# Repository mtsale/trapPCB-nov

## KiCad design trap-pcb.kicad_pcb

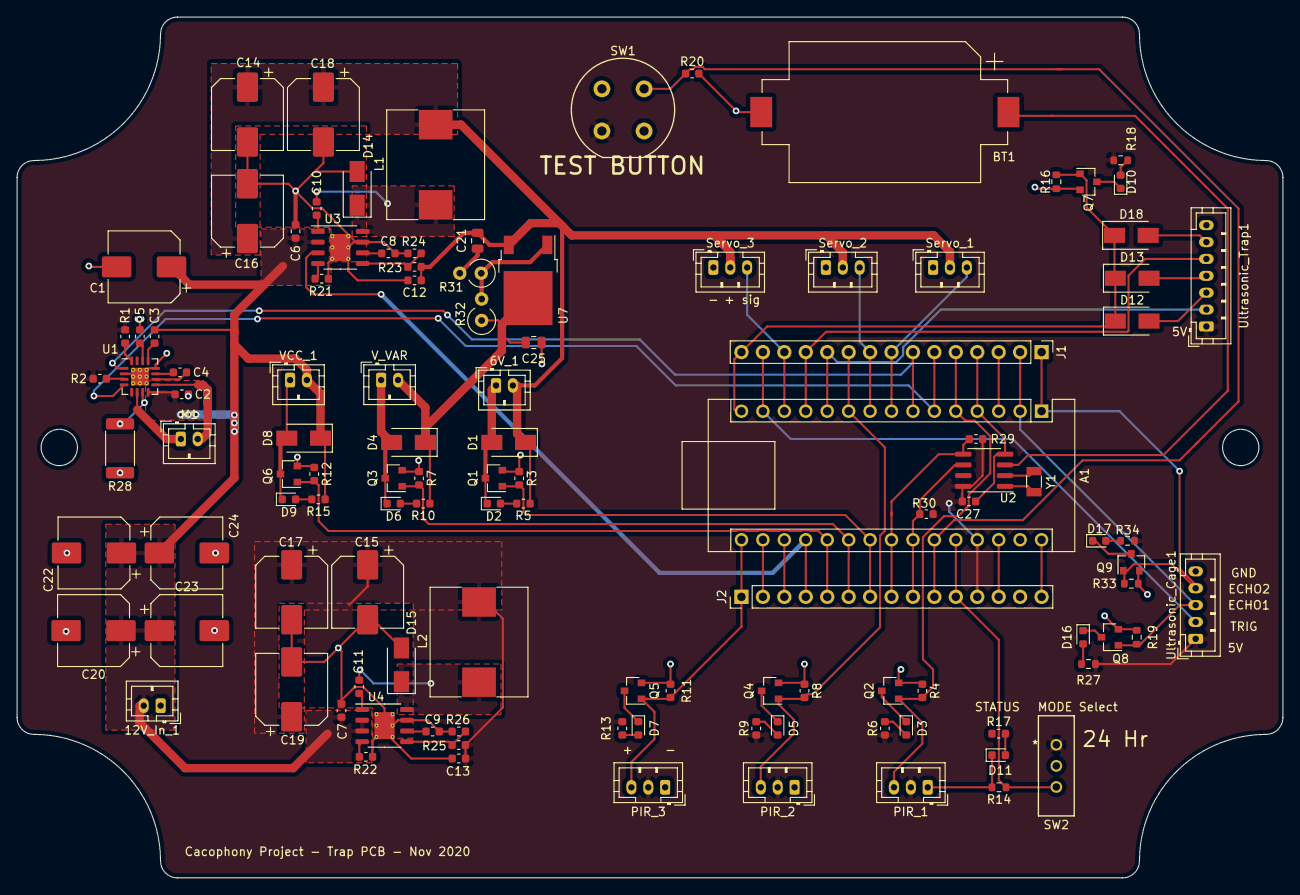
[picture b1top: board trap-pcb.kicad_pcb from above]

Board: 2 copper layers, 150.0 x 102.0 mm, 116 parts (0 on the bottom side), 77 nets.

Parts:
6V_1: CONN HEADER VERT 2POS 2MM; JST_PH_B2B-PH-K_1x02_P2.00mm_Vertical
12V_In_1: Conn_01x02; JST_PH_B2B-PH-K_1x02_P2.00mm_Vertical
A1: Arduino_Nano_v3.x; Arduino_Nano
BT1: Battery_Cell; BatteryHolder_Keystone_1060_1x2032
C1, C14, C15, C16, C17, C18, C19, C20, C22, C23, C24: 220uF; CP_Elec_8x10
C2, C3, C4, C27: 0.1uF; C_0603_1608Metric
C5: 0.22uF; C_0603_1608Metric
C6, C7: 4.7uF; C_0603_1608Metric
C8, C9: 47nF; C_0603_1608Metric
C10, C11: 100nF; C_0603_1608Metric
C12, C13: 1uF; C_0603_1608Metric
C21, C25: 22uF; C_0805_2012Metric
D1, D4, D8, D12, D13, D18: D; D_SMA
D2, D3, D5, D6, D7, D9, D10, D11, D16, D17: LED; LED_0603_1608Metric
D14, D15: D_Shockley; D_SMA
H1, H2: MountingHole; MountingHole_4.3mm_M4
J1, J2: Conn_01x15; PinHeader_1x15_P2.54mm_Vertical
L1, L2: 15uH; MWSA1004
M1: Motor_DC; JST_PH_B2B-PH-K_1x02_P2.00mm_Vertical
PIR_1, PIR_2, PIR_3: Conn_01x03; JST_PH_B3B-PH-K_1x03_P2.00mm_Vertical
Q1, Q2, Q3, Q4, Q5, Q6, Q7, Q8, Q9: Q_NMOS_GSD; SOT-23
R1, R2, R3, R4, R7, R8, R11, R12, R16, R19, R33: 100K; R_0603_1608Metric
R5, R6, R9, R10, R13, R14, R17, R18, R20, R27, R34: 470R; R_0603_1608Metric
R15: 1K; R_0603_1608Metric
R21, R22: 49K9; R_0603_1608Metric
R23: 69.8K; R_0603_1608Metric
R24, R26, R29, R30: 10K; R_0603_1608Metric
R25: 56K; R_0603_1608Metric
R28: 0.2R; R_2512_6332Metric
R31, R32: R; R_Axial_DIN0309_L9.0mm_D3.2mm_P2.54mm_Vertical
SW1: SW_DIP_x02; Push_E-Switch_KS01Q01
SW2: EG1218
Servo_1, Servo_2, Servo_3: Conn_01x03; JST_PH_B3B-PH-K_1x03_P2.00mm_Vertical
U1: DRV8800RTY; Texas_S-PWQFN-N16_EP2.1x2.1mm_ThermalVias
U2: DS1307ZN+; SOIC-8_3.9x4.9mm_P1.27mm
U3, U4: LMR16030; HTSOP-8-1EP_3.9x4.9mm_P1.27mm_EP2.4x3.2mm_ThermalVias
U7: LM317_TO-252; TO-252-2
Ultrasonic_Cage1: Conn_01x05; JST_PH_B5B-PH-K_1x05_P2.00mm_Vertical
Ultrasonic_Trap1: Conn_01x07; JST_PH_B7B-PH-K_1x07_P2.00mm_Vertical
VCC_1: CONN HEADER VERT 2POS 2MM; JST_PH_B2B-PH-K_1x02_P2.00mm_Vertical
V_VAR: CONN HEADER VERT 2POS 2MM; JST_PH_B2B-PH-K_1x02_P2.00mm_Vertical
Y1: 32.769KHz; Crystal_SMD_3215-2Pin_3.2x1.5mm

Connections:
+5V: A1.27, C13.1, C15.1, C17.1, C19.1, C27.1, J2.12, L2.2, PIR_1.2, PIR_2.2, PIR_3.2, R1.2, R2.2, R6.1, R9.1, R13.1, R18.1, R25.1, R27.1, R29.1, R30.1, R34.1, SW1.3, SW2.1, U2.8, Ultrasonic_Cage1.1, Ultrasonic_Trap1.1
+6V: 6V_1.2, C12.1, C14.1, C16.1, C18.1, C21.1, D1.1, L1.2, R5.1, R23.1, Servo_1.2, Servo_2.2, Servo_3.2, U7.3
/3.3V_1: A1.21, J2.6, Q3.1, R7.1
/6V_1: A1.22, J2.7, Q1.1, R3.1
/6V_ENABLE: A1.19, J2.4, U3.3
/ECHO_CAGE: A1.2, J1.2, Q8.1, R19.1, Ultrasonic_Cage1.3
/ECHO_CAGE2: A1.1, J1.1, Q9.1, R33.1, Ultrasonic_Cage1.4
/ECHO_MAIN: A1.15, D12.1, D13.1, D18.1, J1.15, Q7.1, R16.1
/MODE_SWITCH: A1.26, J2.11, R14.1, SW2.3
/Motor_Direction: A1.7, J1.7, U1.1
/Motor_Enable: A1.6, J1.6, U1.4
/PIR_1: A1.5, J1.5, PIR_1.3, Q2.1, R4.1
/PIR_2: A1.10, J1.10, PIR_2.3, Q4.1, R8.1
/PIR_3: A1.16, J2.1, PIR_3.3, Q5.1, R11.1
/SCL: A1.24, J2.9, R30.2, U2.6
/SDA: A1.23, J2.8, R29.2, U2.5
/Servo_1: A1.8, J1.8, Servo_1.3
/Servo_2: A1.9, J1.9, Servo_2.3
/Servo_3: A1.13, J1.13, Servo_3.3
/TRIGGER_CAGE: A1.14, J1.14, Ultrasonic_Cage1.2
/TRIGGER_F1: A1.11, J1.11, Ultrasonic_Trap1.2
/TRIGGER_F2: A1.12, J1.12, Ultrasonic_Trap1.5
/Test_Button: A1.25, J2.10, R20.1, SW1.2
/VCC_1: A1.20, J2.5, Q6.1, R12.1
GND: 12V_In_1.1, A1.4, A1.29, BT1.2, C1.2, C2.2, C5.2, C6.2, C7.2, C8.2, C9.2, C12.2, C13.2, C14.2, C15.2, C16.2, C17.2, C18.2, C19.2, C20.2, C21.2, C22.2, C23.2, C24.2, C25.2, C27.2, D11.1, D14.2, D15.2, J1.4, J2.14, PIR_1.1, PIR_2.1, PIR_3.1, Q1.2, Q2.2, Q3.2, Q4.2, Q5.2, Q6.2, Q7.2, Q8.2, Q9.2, R3.2, R4.2, R7.2, R8.2, R11.2, R12.2, R14.2, R16.2, R19.2, R20.2, R21.2, R22.2, R24.2, R26.2, R28.2, R31.2, R33.2, Servo_1.1, Servo_2.1, Servo_3.1, U1.2, U1.12, U1.17, U2.4, U3.7, U3.9, U4.7, U4.9, Ultrasonic_Cage1.5, Ultrasonic_Trap1.7
unnamed: 6V_1.1, D1.2, D2.1, Q1.3
unnamed: A1.3, J1.3
unnamed: A1.17, J2.2
unnamed: A1.18, J2.3
unnamed: A1.28, J2.13
unnamed: A1.30, J2.15
unnamed: BT1.1, U2.3
unnamed: C3.2, U1.13
unnamed: C4.1, U1.10
unnamed: C4.2, U1.11
unnamed: C5.1, U1.14
unnamed: C8.1, U3.6
unnamed: C9.1, U4.6
unnamed: C10.1, D14.1, L1.1, U3.8
unnamed: C10.2, U3.1
unnamed: C11.1, D15.1, L2.1, U4.8
unnamed: C11.2, U4.1
unnamed: D2.2, R5.2
unnamed: D3.1, Q2.3
unnamed: D3.2, R6.2
unnamed: D4.2, D6.1, Q3.3, V_VAR.1
unnamed: D5.1, Q4.3
unnamed: D5.2, R9.2
unnamed: D6.2, R10.2
unnamed: D7.1, Q5.3
unnamed: D7.2, R13.2
unnamed: D8.2, D9.1, Q6.3, VCC_1.1
unnamed: D9.2, R15.2
unnamed: D10.1, Q7.3
unnamed: D10.2, R18.2
unnamed: D11.2, R17.2
unnamed: D12.2, Ultrasonic_Trap1.3
unnamed: D13.2, Ultrasonic_Trap1.4
unnamed: D16.1, Q8.3
unnamed: D16.2, R27.2
unnamed: D17.1, Q9.3
unnamed: D17.2, R34.2
unnamed: D18.2, Ultrasonic_Trap1.6
unnamed: M1.1, U1.6
unnamed: M1.2, U1.9
unnamed: R1.1, U1.16
unnamed: R2.1, U1.3
unnamed: R21.1, U3.4
unnamed: R22.1, U4.4
unnamed: R23.2, R24.1, U3.5
unnamed: R25.2, R26.1, U4.5
unnamed: R28.1, U1.7
unnamed: R31.1, R32.2, U7.1
unnamed: U2.1, Y1.1
unnamed: U2.2, Y1.2
VCC: 12V_In_1.2, C1.1, C2.1, C3.1, C6.1, C7.1, C20.1, C22.1, C23.1, C24.1, D8.1, R15.1, U1.8, U3.2, U4.2, U4.3, VCC_1.2
VDD: C25.1, D4.1, R10.1, R32.1, U7.2, V_VAR.2

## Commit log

2020-10-29 Add files via upload
    Initial Commit
2020-10-30 DRC Fixes
    Fixed DRC errors. Changed connectors to JST.
2020-11-01 Updated 3D model
2020-11-01 minor layout and routing changes
2020-11-08 Updated JLC and DigiKey parts

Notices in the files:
parts and their libraries:
Copyright 2016 Accelerated Designs. All rights reserved.
